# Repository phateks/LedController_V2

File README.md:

# LED Controller (ESP32-C3-Mini)

<table>
	<tr>
		<td></td>
		<td></td>
	</tr>
</table>

> **_NOTE:_** Add in Kicad the "desk" library 

## Power
- Input: 12 or 24 VDC on J1 connector

> **_NOTE:_** This version can run up to 5A !!

## Connections for Digital LED
- DO (DATA) 
- LED+ = VCC
- LED- = GND

## Connections for Classic LED
- LED+ = VCC
- Dim- = GND

## External Switch (Momentary)

- S1 - Dim down
- S2 - Dim up
- Com - Second connection on the switch (common for both)

## GPIO Config

- IO4: DATA LED
- IO5: PWM LED
- IO6: Dim Up
- IO7: Dim Down
- TXD0/RXD0: 
- EN: reset/enable
- BOOT: bootloader (IO09)

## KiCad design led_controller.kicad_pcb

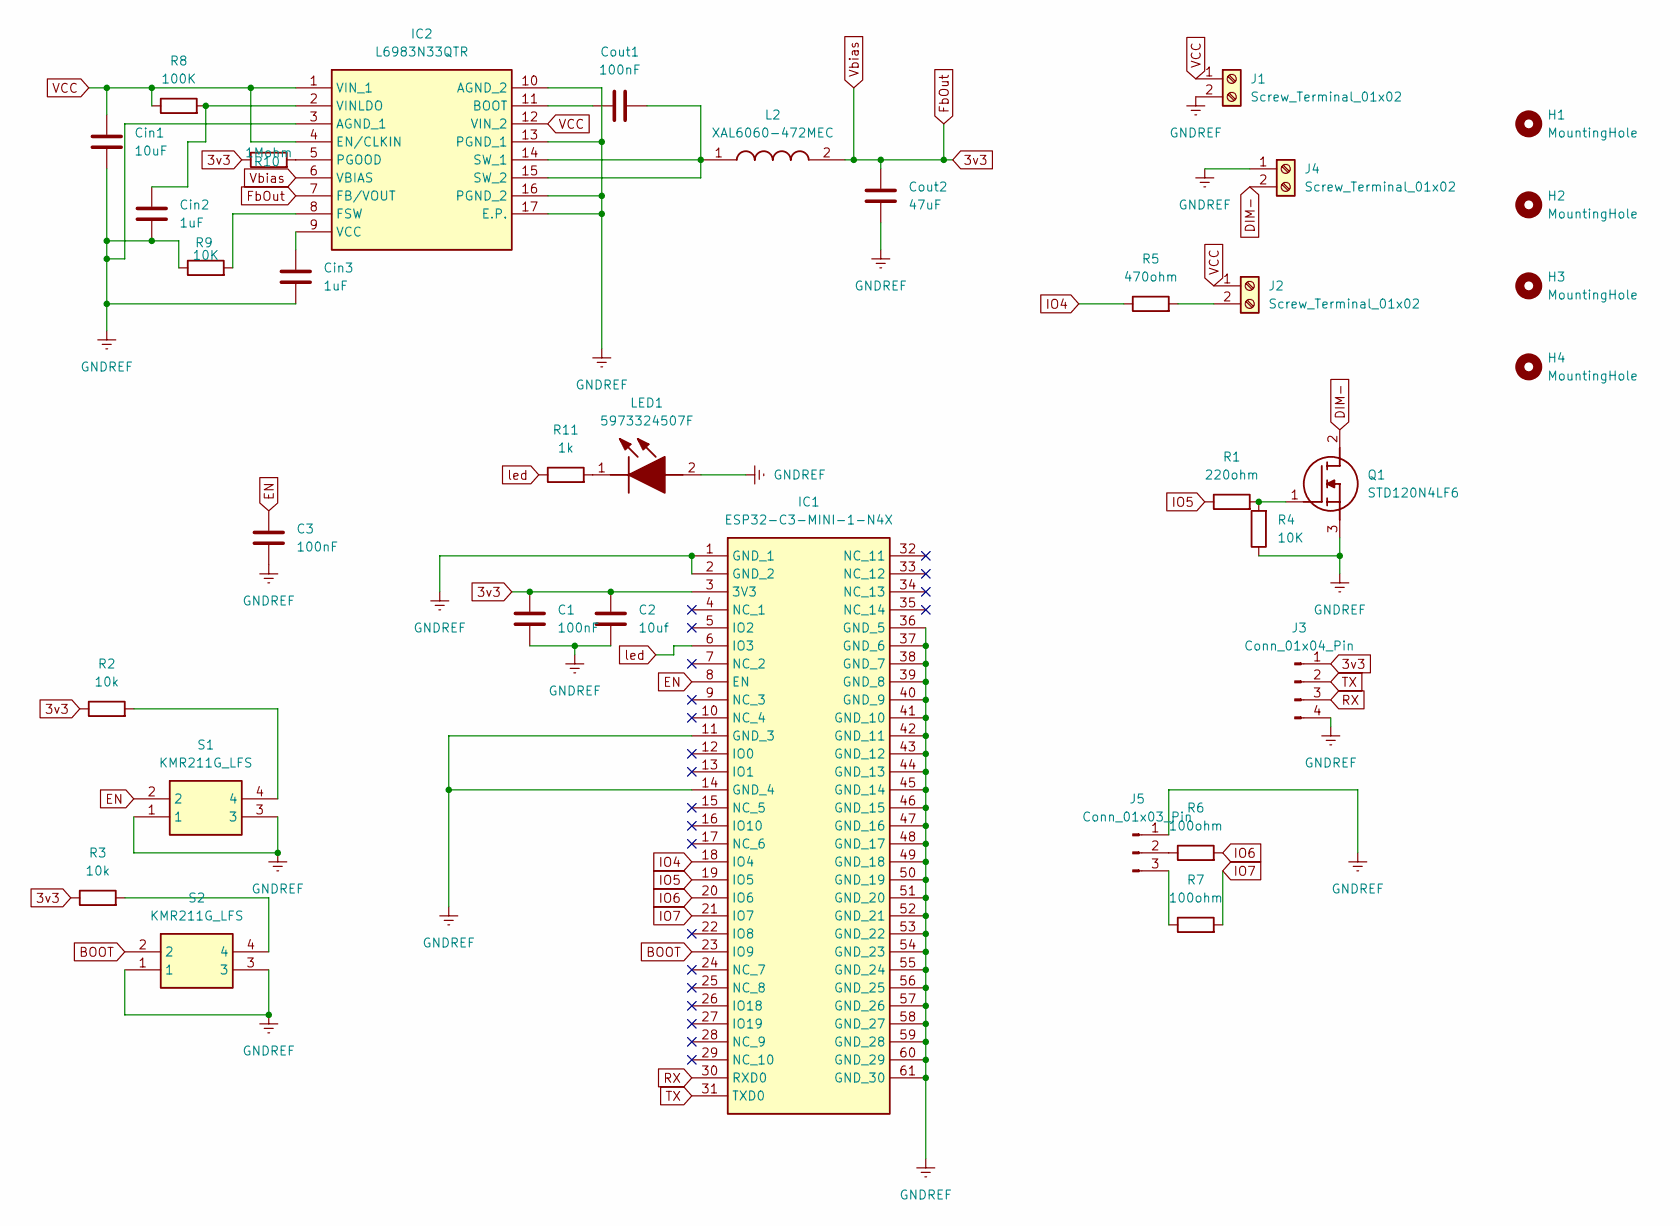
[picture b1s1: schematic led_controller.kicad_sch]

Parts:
C1, C3: 100nF; C_1206_3216Metric_Pad1.33x1.80mm_HandSolder
C2: 10uf; C_1206_3216Metric_Pad1.33x1.80mm_HandSolder
Cin1: 10uF; C_1206_3216Metric_Pad1.33x1.80mm_HandSolder
Cin2, Cin3: 1uF; C_1206_3216Metric_Pad1.33x1.80mm_HandSolder
Cout1: 100nF; C_1206_3216Metric_Pad1.33x1.80mm_HandSolder
Cout2: 47uF; C_1206_3216Metric_Pad1.33x1.80mm_HandSolder
H1, H2, H3, H4: MountingHole; MountingHole_3.2mm_M3
IC1: ESP32-C3-MINI-1-N4X; ESP32C3MINI1N4X; Manufacturer_Part_Number ESP32-C3-MINI-1-N4X
IC2: L6983N33QTR; Manufacturer_Part_Number L6983N33QTR; Mouser Part Number 511-L6983N33QTR
J1, J2, J4: Screw_Terminal_01x02; TerminalBlock_bornier-2_P5.08mm
J3: Conn_01x04_Pin; JST_EH_B4B-EH-A_1x04_P2.50mm_Vertical
J5: Conn_01x03_Pin; JST_EH_S3B-EH_1x03_P2.50mm_Horizontal
L2: XAL6060-472MEC; XAL6060472MEC; Manufacturer_Part_Number XAL6060-472MEC; Mouser Part Number 994-XAL6060-472MEC
LED1: 5973324507F; Manufacturer_Part_Number 5973324507F; Mouser Part Number 645-5973324507F
Q1: STD120N4LF6; Manufacturer_Part_Number STD120N4LF6; Mouser Part Number 511-STD120N4LF6
R1: 220ohm; R_0805_2012Metric_Pad1.20x1.40mm_HandSolder
R2, R3: 10k; R_0805_2012Metric_Pad1.20x1.40mm_HandSolder
R4, R9: 10K; R_0805_2012Metric_Pad1.20x1.40mm_HandSolder
R5: 470ohm; R_0805_2012Metric_Pad1.20x1.40mm_HandSolder
R6, R7: 100ohm; R_0805_2012Metric_Pad1.20x1.40mm_HandSolder
R8: 100K; R_0805_2012Metric_Pad1.20x1.40mm_HandSolder
R10: 1Mohm; R_0805_2012Metric_Pad1.20x1.40mm_HandSolder
R11: 1k; R_0805_2012Metric_Pad1.20x1.40mm_HandSolder
S1, S2: KMR211G_LFS; KMR_2; Manufacturer_Part_Number KMR211G LFS; Mouser Part Number 611-KMR211G-LFS

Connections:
3v3: C1.1, C2.1, Cout2.1, IC1.3 (3V3), IC2.6 (VBIAS), IC2.7 (FB/VOUT), J3.1, L2.2, R2.1, R3.1, R10.1
BOOT: IC1.23 (IO9), S2.2
DIM-: J4.2, Q1.2 (D)
EN: C3.1, IC1.8 (EN), S1.2
GNDREF: C1.2, C2.2, C3.2, Cin1.2, Cin2.2, Cin3.2, Cout2.2, IC1.1 (GND_1), IC1.2 (GND_2), IC1.11 (GND_3), IC1.14 (GND_4), IC1.36 (GND_5), IC1.37 (GND_6), IC1.38 (GND_7), IC1.39 (GND_8), IC1.40 (GND_9), IC1.41 (GND_10), IC1.42 (GND_11), IC1.43 (GND_12), IC1.44 (GND_13), IC1.45 (GND_14), IC1.46 (GND_15), IC1.47 (GND_16), IC1.48 (GND_17), IC1.49 (GND_18), IC1.50 (GND_19), IC1.51 (GND_20), IC1.52 (GND_21), IC1.53 (GND_22), IC1.54 (GND_23), IC1.55 (GND_24), IC1.56 (GND_25), IC1.57 (GND_26), IC1.58 (GND_27), IC1.59 (GND_28), IC1.60 (GND_29), IC1.61 (GND_30), IC2.3 (AGND_1), IC2.10 (AGND_2), IC2.13 (PGND_1), IC2.16 (PGND_2), IC2.17 (E.P.), J1.2, J3.4, J4.1, J5.1, LED1.2 (A), Q1.3 (S), R4.1, R9.1, S1.1, S1.3, S2.1, S2.3
IO4: IC1.18 (IO4), R5.1
IO5: IC1.19 (IO5), R1.1
IO6: IC1.20 (IO6), R6.2
IO7: IC1.21 (IO7), R7.2
unnamed: Cout1.1, IC2.11 (BOOT)
unnamed: IC2.8 (FSW), R9.2
unnamed: IC2.5 (PGOOD), R10.2
unnamed: Cout1.2, IC2.14 (SW_1), IC2.15 (SW_2), L2.1
unnamed: Cin3.1, IC2.9 (VCC)
unnamed: Cin2.1, IC2.2 (VINLDO), R8.2
unnamed: J2.2, R5.2
unnamed: J5.2, R6.1
unnamed: J5.3, R7.1
unnamed: LED1.1 (K), R11.2
unnamed: Q1.1 (G), R1.2, R4.2
unnamed: R2.2, S1.4
unnamed: R3.2, S2.4
RX: IC1.30 (RXD0), J3.3
TX: IC1.31 (TXD0), J3.2
VCC: Cin1.1, IC2.1 (VIN_1), IC2.4 (EN/CLKIN), IC2.12 (VIN_2), J1.1, J2.1, R8.1
led: IC1.6 (IO3), R11.1

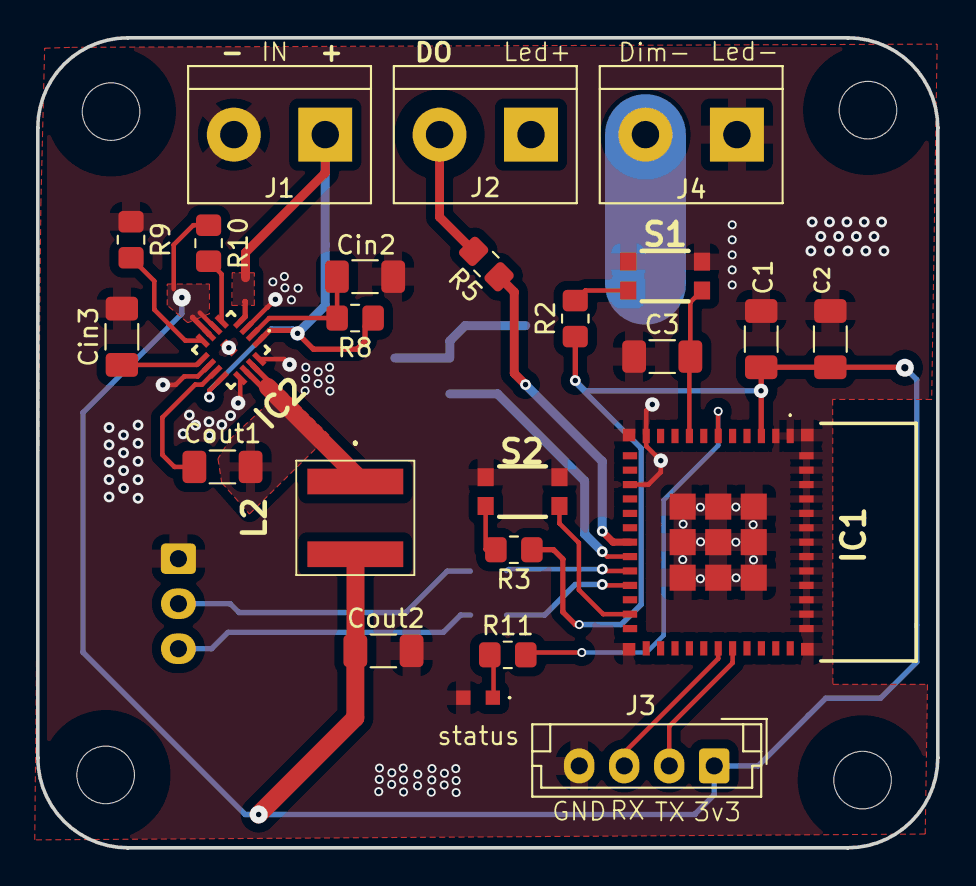
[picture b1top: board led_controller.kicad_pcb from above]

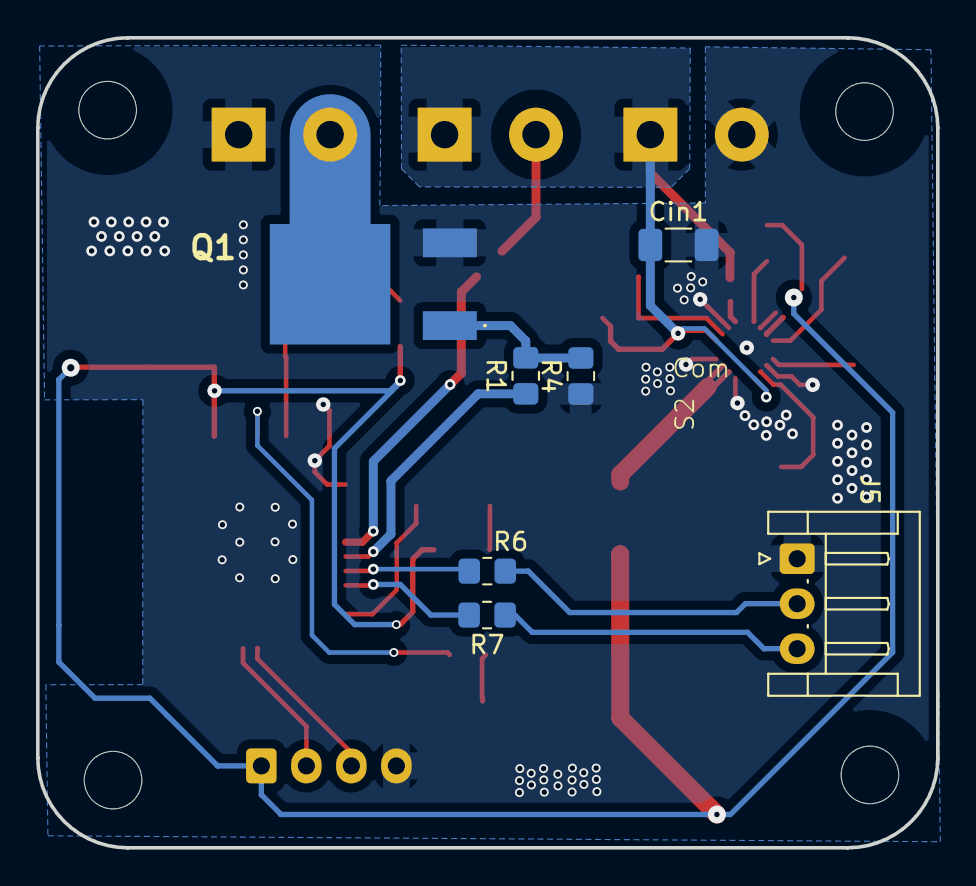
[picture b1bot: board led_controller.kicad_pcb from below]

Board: 2 copper layers, 50.0 x 45.0 mm, 35 parts (7 on the bottom side), 26 nets.

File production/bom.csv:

Designator;Footprint;Quantity;Value;LCSC Part #
C1, C3, COUT1;1206;3;100nF;C1206C104J5RAC7800
C2, CIN1;1206;2;10uf;KGM31HR51H106KU
CIN2, CIN3;1206;2;1uF;KGM31HR71H105JU
COUT2;1206;1;47uF;GRM31CR61A476KE15L
IC1;ESP32C3MINI1N4X;1;ESP32-C3-MINI-1-N4X;ESP32-C3-MINI-1-N4X
IC2;L6983N33QTR;1;L6983N33QTR;L6983N33QTR
J1, J2, J4;TerminalBlock_bornier-2_P5.08mm;3;Screw_Terminal_01x02;
J3;JST_EH_B4B-EH-A_1x04_P2.50mm_Vertical;1;Conn_01x04_Pin;
J5;JST_EH_S3B-EH_1x03_P2.50mm_Horizontal;1;Conn_01x03_Pin;
L2;XAL6060472MEC;1;XAL6060-472MEC;XAL6060-472MEC
LED1;5973324507F;1;5973324507F;5973324507F
Q1;STD120N4LF6;1;STD120N4LF6;
R1;0805;1;220ohm;AA0805FR-07220RL
R10;0805;1;1Mohm;RT0805FRE131ML
R11;0805;1;1k;MCU08050C1001FP500
R2, R3, R4, R9;0805;4;10k;CRCW080510K0FKEA
R5;0805;1;470ohm;MCU08050C4700FP500
R6, R7;0805;2;100ohm;RT0805FRE13100RL
R8;0805;1;100K;CRCW0805100KFKEA
S1, S2;KMR_2;2;KMR211G_LFS;KMR211G_LFS

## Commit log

2026-03-27 Update README with additional power note
    Added note about current capacity for power input.
2026-03-27 Format README.md with proper Markdown syntax
